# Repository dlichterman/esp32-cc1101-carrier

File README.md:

# ESP32 + CC1101 carrier board

A 95 x 55 mm two-layer KiCad carrier that plugs a DOIT ESP32 DevKit V1 (30-pin) and a CC1101 433 MHz breakout (2x4 header, edge-launch SMA) together over SPI, with a matching 3D-printed case. It is not tied to any one firmware: use it for ESPHome, Arduino, MicroPython or anything else that talks to a CC1101 over SPI.

Open `esp32_cc1101_carrier.kicad_pro` in KiCad 10 (rev B files are saved in KiCad 10 format; rev A was KiCad 7).
Project-local libraries are in `libs/` (VictorLamoine ESP32_DevKit_V1_DOIT symbol + footprint + STEP, BSD-with-attribution, see libs/VL_LICENSE.txt).
`build.py` regenerates everything (run with the python that has `pcbnew`; works with KiCad 7 and 10). On Windows set `KICAD_FP_DIR` / `KICAD_SYM_DIR` to KiCad's `share/kicad/footprints` and `share/kicad/symbols`.

| Signal | ESP32 GPIO | CC1101 header pin |
|---|---|---|
| SCK  | 18 | 5 |
| MOSI | 23 | 6 |
| MISO | 19 | 7 |
| CSN  | 22 | 4 |
| GDO0 | 21 | 3 |
| VCC  | 3V3 | 2 |
| GND  | GND | 1 |
GDO2 (pin 8) -> GPIO4 (not a strapping pin). None of the GPIOs used are strapping pins, so boot behaviour is unaffected.

Example ESPHome SPI/CC1101 pin settings: `clk_pin: GPIO18`, `mosi_pin: GPIO23`, `miso_pin: GPIO19`, `cs_pin: GPIO22`, `gdo0_pin: GPIO21`, `gdo2_pin: GPIO4`. The pin map is set at the top of `build.py` if you need a different one for another project.

Fab files: `fab/` (Gerbers + separate PTH/NPTH drill files, 2 layers, 95 x 55 mm, 1.6 mm).

## Capacitors
All through-hole and optional: populate only what you need.

| Ref | Value | Type | Rail | Size | Location |
|---|---|---|---|---|---|
| C1 | 470 µF, 16 V | Aluminium electrolytic, radial | VIN | D8 mm, 3.5 mm pitch, about 12.5 mm tall | Left of the ESP32 |
| C2 | 100 nF, 50 V | Ceramic (MLCC), X7R | VIN | 5 mm lead pitch (disc up to 5 x 2.5 mm) | Left of the ESP32 |
| C3 | 22 µF, 16 V | Aluminium electrolytic, radial | 3V3 | D5 mm, 2 mm pitch, about 11.5 mm tall | Above the CC1101 header |
| C4 | 100 nF, 50 V | Ceramic (MLCC), X7R | 3V3 | 5 mm lead pitch (disc up to 5 x 2.5 mm) | Above the CC1101 header, by its VCC pin |

- Electrolytics are polarised: the square pad (pad 1) is + (VIN or 3V3).
- C3 can be anything from 10 to 47 µF, as long as it is D5 mm or smaller with 2 mm pitch; a wider can would reach under the CC1101 module. Heights above are what the case model assumes (the lid is 18 mm above the board).
- Fit C1 when powering from VIN through long wires or a battery. On USB power it isn't needed. 470 µF is well over the USB inrush limit (10 µF), which can occasionally upset a strict port or hub at plug-in. If you want it fitted on USB anyway, a smaller value (47–100 µF) is a reasonable compromise.

## Layout notes
- Bottom copper (B.Cu) is a solid GND plane; top copper (F.Cu) carries all SPI signals plus a GND pour, tied together with stitching vias.
- Signals stay on F.Cu except two short hops to B.Cu: SCK (about 4.6 mm) and +3V3 (about 8.9 mm), each through one via pair. The rest of B.Cu is the ground plane.
- The top 9.2 mm of the board (above the ESP32 pin rows, full width) has no ground pour on either layer. One MOSI trace (GPIO23 is the top pin of the right-hand row) runs through that strip for about 22 mm.
- Silkscreen: strokes 0.2 mm, text >= 1.0 mm (JLCPCB DFM rates 0.15 mm only as a warning). Solder-mask expansion 0.05 mm.

## Rev B (current)
- C3 (22 uF, 3V3 bulk cap) moved 2.5 mm toward the top of the board (y 17.5 -> 15.0 mm). Its body now clears the CC1101 breakout's edge by about 0.8 mm (module edge estimated from photos, +/-0.5 mm), so it can stand upright instead of being bent over. Its 3V3 trace is about 2 mm longer; nothing else in the routing changed.
- Silkscreen and title block read rev B.

## Rev A: layout refinement
45° corners, ground stitching along traces and edge, vias ≥2.2 mm from pins, thermal-relief settings, 1.0 mm header holes. See `audit-report.md`, `reports/print_1to1_letter.pdf` / `print_1to1_a4.pdf` for a 1:1 fit check (30 mm ruler; print at Actual size).

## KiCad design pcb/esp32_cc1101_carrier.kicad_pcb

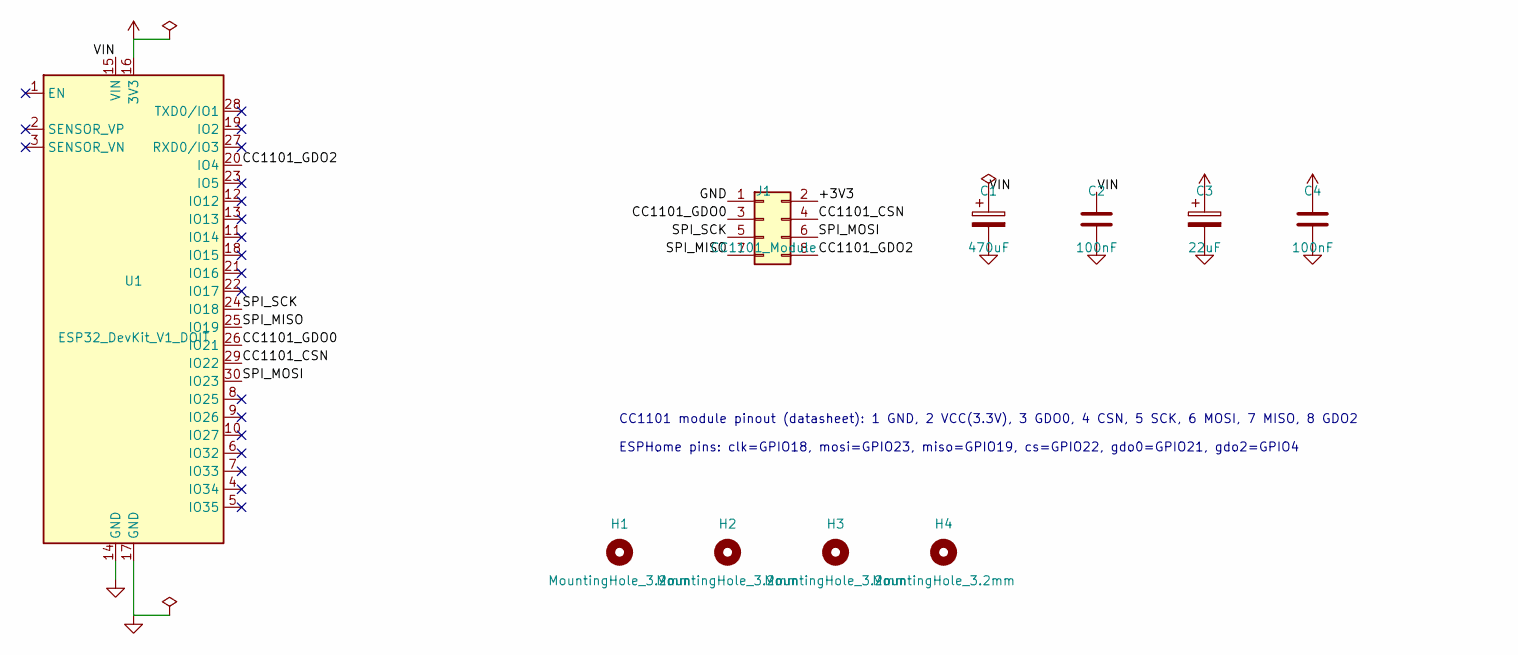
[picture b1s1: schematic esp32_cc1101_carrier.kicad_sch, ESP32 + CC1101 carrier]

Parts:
C1: 470uF; CP_Radial_D8.0mm_P3.50mm
C2, C4: 100nF; C_Disc_D5.0mm_W2.5mm_P5.00mm
C3: 22uF; CP_Radial_D5.0mm_P2.00mm
H1, H2, H3, H4: MountingHole_3.2mm; MountingHole_3.2mm_M3
J1: CC1101_Module; PinHeader_2x04_P2.54mm_Vertical
U1: ESP32_DevKit_V1_DOIT; esp32_devkit_v1_doit

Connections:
+3V3: C3.1, C4.1, J1.2, U1.16 (3V3)
/CC1101_CSN: J1.4, U1.29 (IO22)
/CC1101_GDO0: J1.3, U1.26 (IO21)
/CC1101_GDO2: J1.8, U1.20 (IO4)
/SPI_MISO: J1.7, U1.25 (IO19)
/SPI_MOSI: J1.6, U1.30 (IO23)
/SPI_SCK: J1.5, U1.24 (IO18)
/VIN: C1.1, C2.1, U1.15 (VIN)
GND: C1.2, C2.2, C3.2, C4.2, J1.1, U1.14 (GND), U1.17 (GND)

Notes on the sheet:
CC1101 module pinout (datasheet): 1 GND, 2 VCC(3.3V), 3 GDO0, 4 CSN, 5 SCK, 6 MOSI, 7 MISO, 8 GDO2
ESPHome pins: clk=GPIO18, mosi=GPIO23, miso=GPIO19, cs=GPIO22, gdo0=GPIO21, gdo2=GPIO4

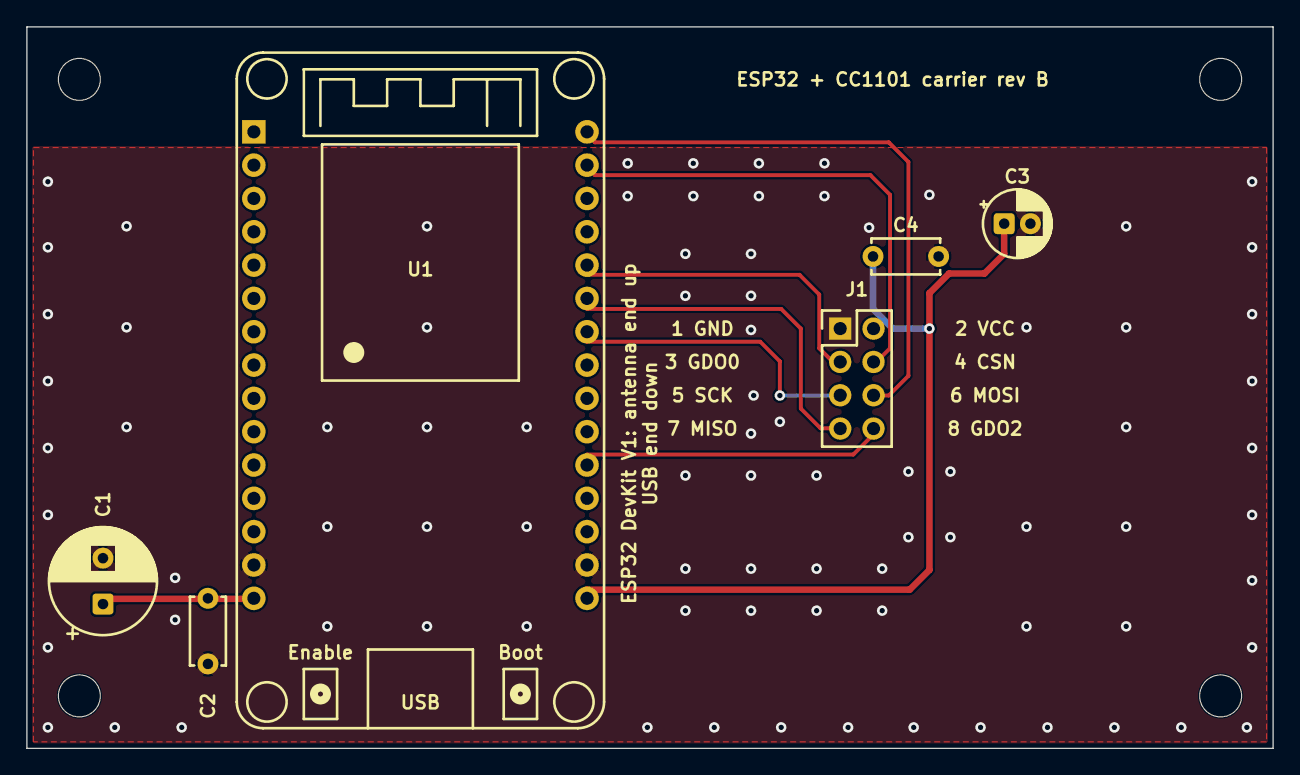
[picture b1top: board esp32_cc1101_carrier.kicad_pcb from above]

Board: 2 copper layers, 95.0 x 55.0 mm, 10 parts (0 on the bottom side), 9 nets.

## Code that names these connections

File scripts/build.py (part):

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            "SPI_MISO": [25],       # IO19
            "CC1101_CSN": [29],     # IO22
            "CC1101_GDO0": [26],    # IO21
            "CC1101_GDO2": [20],    # IO4 (not a strapping pin)
            "+3V3": [16], "GND": [14, 17]}
CC_PINS = {1: "GND", 2: "+3V3", 3: "CC1101_GDO0", 4: "CC1101_CSN", 5: "SPI_SCK", 6: "SPI_MOSI", 7: "SPI_MISO", 8: "CC1101_GDO2"}
CC_NAMES = {1: "GND", 2: "VCC", 3: "GDO0", 4: "CSN", 5: "SCK", 6: "MOSI", 7: "MISO", 8: "GDO2"}
NETS = ["GND", "+3V3", "VIN", "SPI_SCK", "SPI_MOSI", "SPI_MISO", "CC1101_CSN", "CC1101_GDO0", "CC1101_GDO2"]

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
